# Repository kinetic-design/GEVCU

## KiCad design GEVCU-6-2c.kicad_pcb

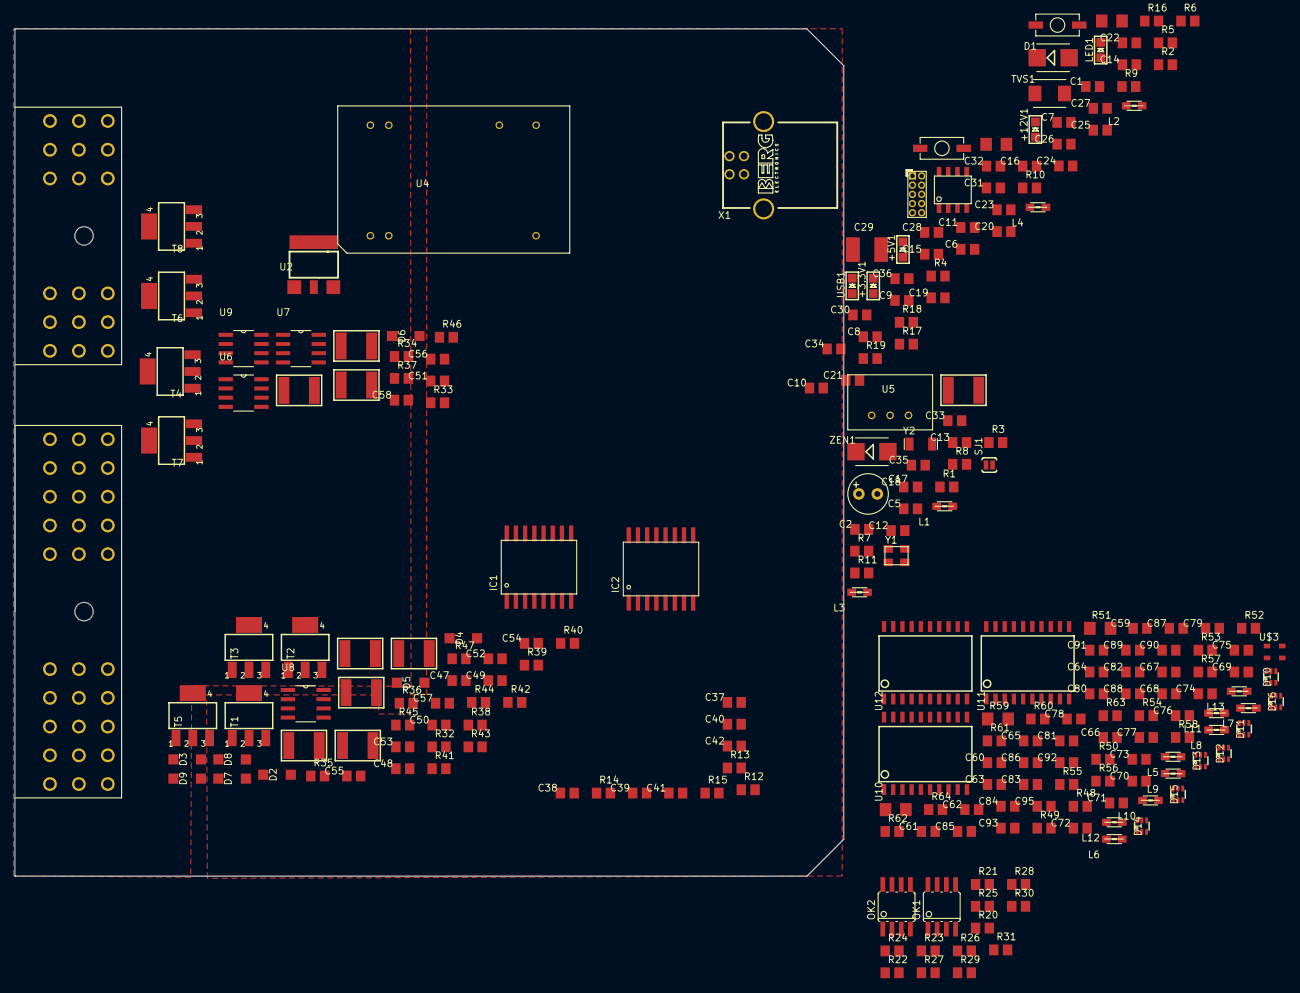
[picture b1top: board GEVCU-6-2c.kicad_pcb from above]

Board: 4 copper layers, 114.3 x 116.8 mm, 233 parts (0 on the bottom side), 163 nets, no tracks yet.

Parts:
+3.3V1, +5V1, +12V1: LED0805; CHIPLED_0805
C1, C10, C11, C12, C15, C16, C19, C21, C22, C23, C24, C25, C26, C27, C28, C30, C31, C32, C35, C37, C38, C41, C42, C47, C48, C49, C50, C51, C52, C53, C54, C63, C64, C70, C72, C74, C82, C83, C84, C85, C86, C87, C89, C91, C93, C95: 0.1u; C0805
C2, C7: 10uF; C0805
C3, C4, C94: 22p; C1206
C5, C6, C8: 22p; C0805
C9: 0.01u; C0805
C13, C14, C18, C33, C36, C55, C56, C57, C58, C71, C73, C75, C88, C90, C92: 10u; C0805
C17: 100u; E2,5-6
C20: 1u; C0805
C29: 0.01u; C1812
C34: 2u; C0805
C39, C40: 47n; C0805
C59, C60, C61, C62, C65, C66, C67: .1u; C0805
C68, C69: 0.033u; C0805
C76, C77, C78, C79, C80, C81: 4.7u; C0805
D1: B360B-13-F; SMB
D2, D3, D4, D5, D6, D7, D8, D9: MBR0520LT; SOD123
D10, D11, D12, D13, D14, D15, D16: BAS70XY; SOT363_PHILIPS
ERASE1: PUCHBUTTON
IC1, IC2: ISO1050DW; DUB-R-PDSO-G8
JTAG1: PINHEAD_PINHD-2X5PASSO127; PINHEAD_2X05_127
L1, L2, L3, L4, L5, L6, L7, L8, L9, L10, L11, L12, L13: MH2029-300Y; 0805
LED1: LED0805; CHIPLED_0805
OK1, OK2: ILD2; SOIC08
PTC1, PTC2, PTC3, PTC4, PTC5, PTC6, PTC7, PTC8, PTC9: 2.5A; PTC1812
R1, R2: 4.7k; R0805
R3, R10, R20, R21, R22, R23, R26, R27, R28, R29: 1k; R0805
R4: 6k8 1%; R0805
R5, R6: 39R 1%; R0805
R7, R16, R17, R18, R19: 100k; R0805
R8, R11: 402R; R0805
R9: 3k3; R0805
R12, R13, R14, R15: 60R; R0805
R24, R25, R30, R31, R32, R33, R34, R35, R36, R37, R38, R39, R64: 10k; R0805
R40, R41, R42, R43, R44, R45, R46, R47: 10; R0805
R48, R50, R54, R57: 14k .1%; R0805
R49, R52, R56, R61, R62: 1k .1%; R0805
R51, R59: 1M 0.1%; R1206
R53, R63: 1.5K 0.1%; R0805
R55, R58: 0R; R0805
R60: 750R .1%; R0805
RESET1: PUCHBUTTON
SJ1: SOLDERJUMPERNO; SJ_2S-NO
T1, T2, T3, T4, T5, T6, T7, T8: NMOSSOT223; SOT223
TVS1: SMBJ15A-TR; SMBJ
U1: CK_CUSTOM_M24M02-DRMN6TP; CK_CUSTOM_SOIC8
U2: LM1117SOT223-WAVE; SOT223-W
U3: ATSAM3X8EA-AU; LQFP144
U4: TRACO
U5: TSR-1
U6, U7, U8, U9: ADUM3221BRZ; SOIC127P600X175-8N
U10, U11, U12: ADE7913; SOIC20
U$1: 581_01_48_005_S
U$3: ASE
USB1: LED0805; CHIPLED_0805
X1: PN61729-S
Y1: 12MHz KX-7 20pF; CRYSTAL-3.2-2.5
Y2: 32.768Khz; ARDUINO_WIFI_SHIELD_V018_TG_RESONATOR_EPSON_FC_145
ZEN1: 1SMB5929BT3G; SMB

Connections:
+3V3: C1.1, C7.1, C9.1, C10.1, C14.1, C15.1, C16.1, C17.+, C19.1, C20.1, C22.1, C23.1, C25.1, C28.1, C34.1, C37.1, C38.1, C41.1, C42.1, C47.1, C48.1, C49.1, C50.1, C51.1, C52.1, C53.1, C54.1, C55.1, C56.1, C57.1, C58.1, C88.1, C89.1, C90.1, C91.1, C92.1, C93.1, C95.2, ERASE1.P$2, IC1.1, IC1.9, IC2.1, IC2.9, JTAG1.1, L1.1, L3.1, L4.1, PTC1.P$1, R1.1, R2.1, R7.2, R9.2, R10.2, R11.2, R16.2, R17.2, R18.2, R19.2, R24.2, R25.2, R30.2, R31.2, R32.2, R33.2, R34.2, R35.2, R36.2, R37.2, R38.2, R39.2, R64.2, U1.PIN8, U2.2, U3.11, U3.52, U3.57, U3.62, U3.105, U3.125, U4.+VIN1, U4.+VIN2, U4.+VOUT, U5.P$1, U5.P$3, U6.1, U6.8, U7.1, U7.8, U8.1, U8.8, U9.1, U9.8, U10.19, U11.19, U12.19, U$1.P$1, U$1.P$2, U$1.P$7, U$1.P$8, U$1.P$14, U$1.P$15, U$1.P$17, U$1.P$36, U$1.P$37, U$1.P$38, U$3.4
/ACS1: U3.14, U10.18
/ACS2: U3.16, U11.18
/ACS3: U3.22, U12.18
/AIN0: L9.1, U$1.P$19
/AIN1: L5.1, U$1.P$20
/AIN2: L10.1, U$1.P$21
/AIN3: L6.1, U$1.P$22
/AVREF: C11.1, L1.2, U3.75
/Analog/CLKO: U10.12, U11.13, U12.13
/CANH0: IC1.12, R14.2, U$1.P$29
/CANH1: IC2.12, R15.2, U$1.P$31
/CANL0: IC1.13, R12.2, U$1.P$30
/CANL1: IC2.13, R13.2, U$1.P$32
/CANRX0: IC1.3, U3.24
/CANRX1: IC2.3, U3.76
/CANTX0: IC1.6, U3.23
/CANTX1: IC2.6, U3.140
/D2: U3.144, U6.2
/D3: U3.139, U6.3
/D4: U3.137, U7.2
/D5: U3.136, U7.3
/D6: U3.135, U8.2
/D7: U3.134, U8.3
/D8: U3.133, U9.2
/D9: U3.132, U9.3
/D13: R8.2, U3.68
/D48: R22.2, R24.1, U3.97
/D49: R28.2, R30.1, U3.96
/D50: R23.2, R25.1, U3.95
/D51: R29.2, R31.1, U3.94
/D+: R6.1, U3.37, X1.3
/D-: R5.1, U3.38, X1.2
/DIN0: R20.1, U$1.P$25
/DIN1: R26.1, U$1.P$26
/DIN2: R21.1, U$1.P$27
/DIN3: R27.1, U$1.P$28
/DOUT0: PTC6.P$1, U$1.P$4
/DOUT1: PTC7.P$1, U$1.P$10
/DOUT2: PTC8.P$1, U$1.P$5
/DOUT3: PTC9.P$1, U$1.P$16
/DOUT4: PTC2.P$1, U$1.P$11
/DOUT5: PTC3.P$1, U$1.P$6
/DOUT6: PTC4.P$1, U$1.P$12
/DOUT7: PTC5.P$1, U$1.P$18
/DREADY: U3.32, U12.12
/ERASE: ERASE1.P$1, U3.130
/JTAG_RESET: JTAG1.10, R16.1, SJ1.1
/JTAG_TCK: JTAG1.4, R18.1, U3.28
/JTAG_TDI: JTAG1.8, R17.1, U3.29
/JTAG_TDO: JTAG1.6, U3.30
/JTAG_TMS: JTAG1.2, R19.1, U3.31
/MASTER-RESET: C9.2, RESET1.P$2, SJ1.2, U3.47
/MISO: R64.1, U3.108, U10.15, U11.15, U12.15
/MOSFeT/MDRIVE0: R40.2, U6.7
/MOSFeT/MDRIVE1: R41.2, U6.6
/MOSFeT/MDRIVE2: R42.2, U7.7
/MOSFeT/MDRIVE3: R43.2, U7.6
/MOSFeT/MDRIVE4: R44.2, U8.7
/MOSFeT/MDRIVE6: R46.2, U9.7
/MOSFeT/MDRIVE7: R47.2, U9.6
/MOSI: U3.109, U10.16, U11.16, U12.16
/PACK_HIGH: L13.1, U$1.P$23
/PACK_LOW: L7.1, U$1.P$24
/PACK_MID: L8.1, U$1.P$33
/SCK: U3.110, U10.17, U11.17, U12.17
/SCL: R1.2, U1.PIN6, U3.87
/SDA: R2.2, U1.PIN5, U3.86
/SHUNT_H: L12.2, U$1.P$35
/SHUNT_L: L11.2, U$1.P$34
/VBG: C8.1, R4.2, U3.40
/VBUS: C2.1, R3.2, U2.3, U3.39, X1.1
/VDDANA: C35.1, C36.1, L3.2, U3.73
/VDDOUT: C18.1, C21.1, C24.1, C26.1, C27.1, C30.1, C32.1, L2.1, U3.10, U3.45, U3.56, U3.61, U3.104, U3.124
/VDDOUTMI: C31.1, C33.1, L4.2, U3.41
/VDDPLL: C12.1, C13.1, L2.2, U3.34
/VIN(+12V): D1.A, U$1.P$3
/XIN: C4.1, U3.36, Y1.1
/XIN32: C6.1, U3.48, Y2.P$2
/XOUT: C3.1, U3.35, Y1.3
/XOUT32: C5.1, U3.49, Y2.P$1
GND: +3.3V1.C, +5V1.C, +12V1.C, C1.2, C2.2, C3.2, C4.2, C5.2, C6.2, C7.2, C8.2, C10.2, C11.2, C12.2, C13.2, C14.2, C15.2, C16.2, C17.-, C18.2, C19.2, C20.2, C21.2, C22.2, C23.2, C24.2, C25.2, C26.2, C27.2, C28.2, C29.1, C29.2, C30.2, C31.2, C32.2, C33.2, C34.2, C35.2, C36.2, C37.2, C38.2, C39.2, C40.2, C41.2, C42.2, C47.2, C48.2, C49.2, C50.2, C51.2, C52.2, C53.2, C54.2, C55.2, C56.2, C57.2, C58.2, C59.2, C60.2, C62.2, C63.2, C65.2, C66.2, C68.2, C69.2, C76.2, C77.2, C78.2, C79.2, C82.2, C83.2, C84.2, C85.2, C88.2, C89.2, C90.2, C91.2, C92.2, C93.2, C94.2, C95.1, D2.A, D3.A, D4.A, D5.A, D6.A, D7.A, D8.A, D9.A, IC1.2, IC1.7, IC1.8, IC1.10, IC1.15, IC1.16, IC2.2, IC2.7, IC2.8, IC2.10, IC2.15, IC2.16, JTAG1.3, JTAG1.5, JTAG1.9, LED1.C, OK1.2, OK1.4, OK1.5, OK1.7, OK2.2, OK2.4, OK2.5, OK2.7, R4.1, R32.1, R33.1, R34.1, R35.1, R36.1, R37.1, R38.1, R39.1, R49.1, R52.1, R55.1, R58.1, R61.2, R62.2, RESET1.P$1, T1.3, T2.3, T3.3, T4.3, T5.3, T6.3, T7.3, T8.3, TVS1.A, U1.PIN1, U1.PIN2, U1.PIN3, U1.PIN4, U1.PIN7, U2.1, U3.12, U3.33, U3.44, U3.46, U3.54, U3.58, U3.74, U3.106, U3.126, U4.-VIN1, U4.-VIN2, U4.-VOUT, U5.P$2, U6.4, U6.5, U7.4, U7.5, U8.4, U8.5, U9.4, U9.5, U10.10, U10.11, U10.20, U11.10, U11.11, U11.20, U12.11, U12.20, U$1.P$9, U$1.P$13, U$1.P$39, U$1.P$40, U$1.P$41, U$1.P$42, U$1.P$43, U$1.P$44, U$1.P$45, U$1.P$46, U$1.P$47, U$1.P$48, U$3.2, USB1.C, X1.4, Y1.2, Y1.4, ZEN1.A
unnamed: +3.3V1.A, R11.1
unnamed: +5V1.A, R10.1
unnamed: +12V1.A, R9.1
unnamed: C39.1, R12.1, R14.1
unnamed: C40.1, R13.1, R15.1
unnamed: C59.1, D10.6, R48.2, R49.2, U10.3
unnamed: C60.1, D11.6, R50.2, R52.2, U11.3
unnamed: C61.1, D12.6, R51.2, R53.2, U12.3
unnamed: C61.2, C67.2, C80.2, C81.2, C86.2, C87.2, D12.3, D15.3, L8.2, R53.1, R63.2, U12.5, U12.10
unnamed: C62.1, D10.3, D13.3, R55.2, U10.5
unnamed: C63.1, D11.3, D14.3, R58.2, U11.5
unnamed: C64.1, C68.1, D14.6, L11.1, R60.1, U10.6
unnamed: C64.2, C69.1, D14.1, D14.2, R56.1, R60.2, U10.7
unnamed: C65.1, D13.6, R54.1, R61.1, U10.4
unnamed: C66.1, D15.6, R57.1, R62.1, U11.4
unnamed: C67.1, D16.6, R59.1, R63.1, U12.4
unnamed: C70.1, C71.1, U10.1
unnamed: C70.2, C71.2, U10.2
unnamed: C72.1, C73.1, U11.1
unnamed: C72.2, C73.2, U11.2
unnamed: C74.1, C75.1, U12.1
unnamed: C74.2, C75.2, U12.2
unnamed: C76.1, C82.1, U10.9
unnamed: C77.1, C83.1, U10.8
unnamed: C78.1, C84.1, U11.9
unnamed: C79.1, C85.1, U11.8
unnamed: C80.1, C86.1, U12.9
unnamed: C81.1, C87.1, U12.8
unnamed: C94.1, U10.13, U$3.3
unnamed: D1.C, PTC1.P$2, TVS1.C, ZEN1.C
unnamed: D2.C, PTC6.P$2, T1.2, T1.4
unnamed: D3.C, PTC8.P$2, T3.2, T3.4
unnamed: D4.C, PTC9.P$2, T4.2, T4.4
unnamed: D5.C, PTC7.P$2, T2.2, T2.4
unnamed: D6.C, PTC2.P$2, T5.2, T5.4
unnamed: D7.C, PTC3.P$2, T6.2, T6.4
unnamed: D8.C, PTC4.P$2, T7.2, T7.4
unnamed: D9.C, PTC5.P$2, T8.2, T8.4
unnamed: D10.1, D10.5
unnamed: D10.2, D10.4
unnamed: D11.1, D11.5
unnamed: D11.2, D11.4
unnamed: D12.1, D12.5
unnamed: D12.2, D12.4
unnamed: D13.1, D13.5
unnamed: D13.2, D13.4
unnamed: D14.4, D15.2
unnamed: D14.5, D15.1
unnamed: D15.4, D16.2
unnamed: D15.5, D16.1
unnamed: L5.2, R48.1
unnamed: L6.2, R50.1
unnamed: L7.2, R51.1
unnamed: L9.2, R54.2
unnamed: L10.2, R57.2
unnamed: L12.1, R56.2
unnamed: L13.2, R59.2
unnamed: LED1.A, R8.1
unnamed: OK1.1, R20.2
unnamed: OK1.3, R26.2
unnamed: OK1.6, R28.1
unnamed: OK1.8, R22.1
unnamed: OK2.1, R21.2
unnamed: OK2.3, R27.2
unnamed: OK2.6, R29.1
unnamed: OK2.8, R23.1
unnamed: R3.1, USB1.A
unnamed: R5.2, U3.43
unnamed: R6.2, U3.42
unnamed: R7.1, U3.53
unnamed: R40.1, T1.1
unnamed: R41.1, T2.1
unnamed: R42.1, T3.1
unnamed: R43.1, T4.1
unnamed: R44.1, T5.1
unnamed: R45.1, T6.1
unnamed: R45.2, U8.6
unnamed: R46.1, T7.1
unnamed: R47.1, T8.1
unnamed: U11.6, U11.7
unnamed: U12.6, U12.7

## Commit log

2019-04-26 initial commit
    GEVCU w modifications for helicopter
